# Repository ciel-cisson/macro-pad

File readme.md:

**Présentation du Projet**

Partie Composants 3D

Partie Cuivre 3D

👉 [Liste des composants (à mettre sur github pages)](documents/composants/liste.html)

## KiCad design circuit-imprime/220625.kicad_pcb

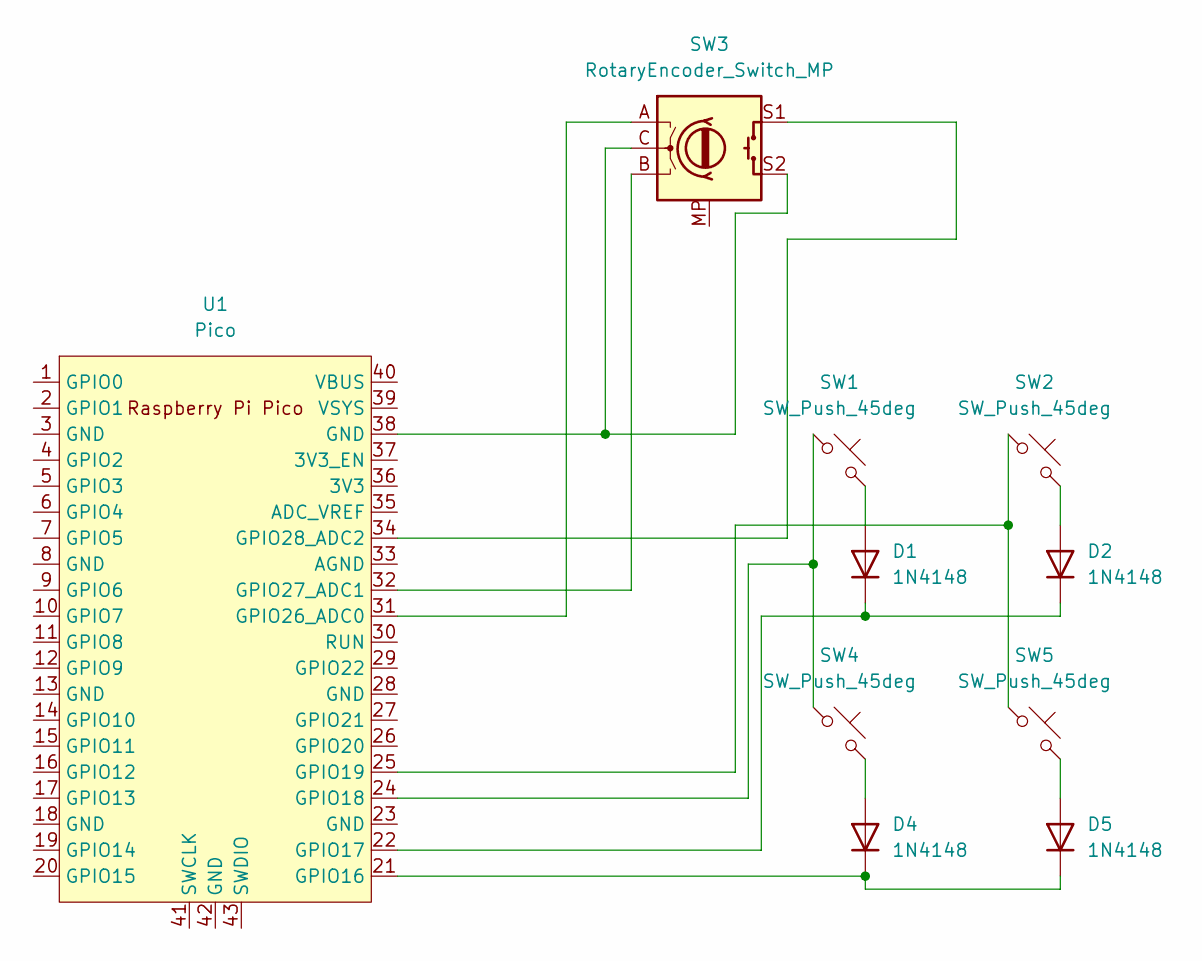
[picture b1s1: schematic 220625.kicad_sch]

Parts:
D1, D2, D4, D5: 1N4148; D_DO-35_SOD27_P7.62mm_Horizontal
SW1, SW2, SW4, SW5: SW_Push_45deg; SW_Cherry_MX_Plate_1.00u
SW3: RotaryEncoder_Switch_MP; RotaryEncoder_Alps_EC11E-Switch_Vertical_H20mm
U1: Pico; RPi_Pico_SMD_TH

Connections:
unnamed: D1.2 (A), SW1.2
unnamed: D1.1 (K), D2.1 (K), U1.22 (GPIO17)
unnamed: D2.2 (A), SW2.2
unnamed: D4.2 (A), SW4.2
unnamed: D4.1 (K), D5.1 (K), U1.21 (GPIO16)
unnamed: D5.2 (A), SW5.2
unnamed: SW3.C, SW3.S2, U1.38 (GND)
unnamed: SW1.1, SW4.1, U1.24 (GPIO18)
unnamed: SW2.1, SW5.1, U1.25 (GPIO19)
unnamed: SW3.A, U1.31 (GPIO26_ADC0)
unnamed: SW3.B, U1.32 (GPIO27_ADC1)
unnamed: SW3.S1, U1.34 (GPIO28_ADC2)

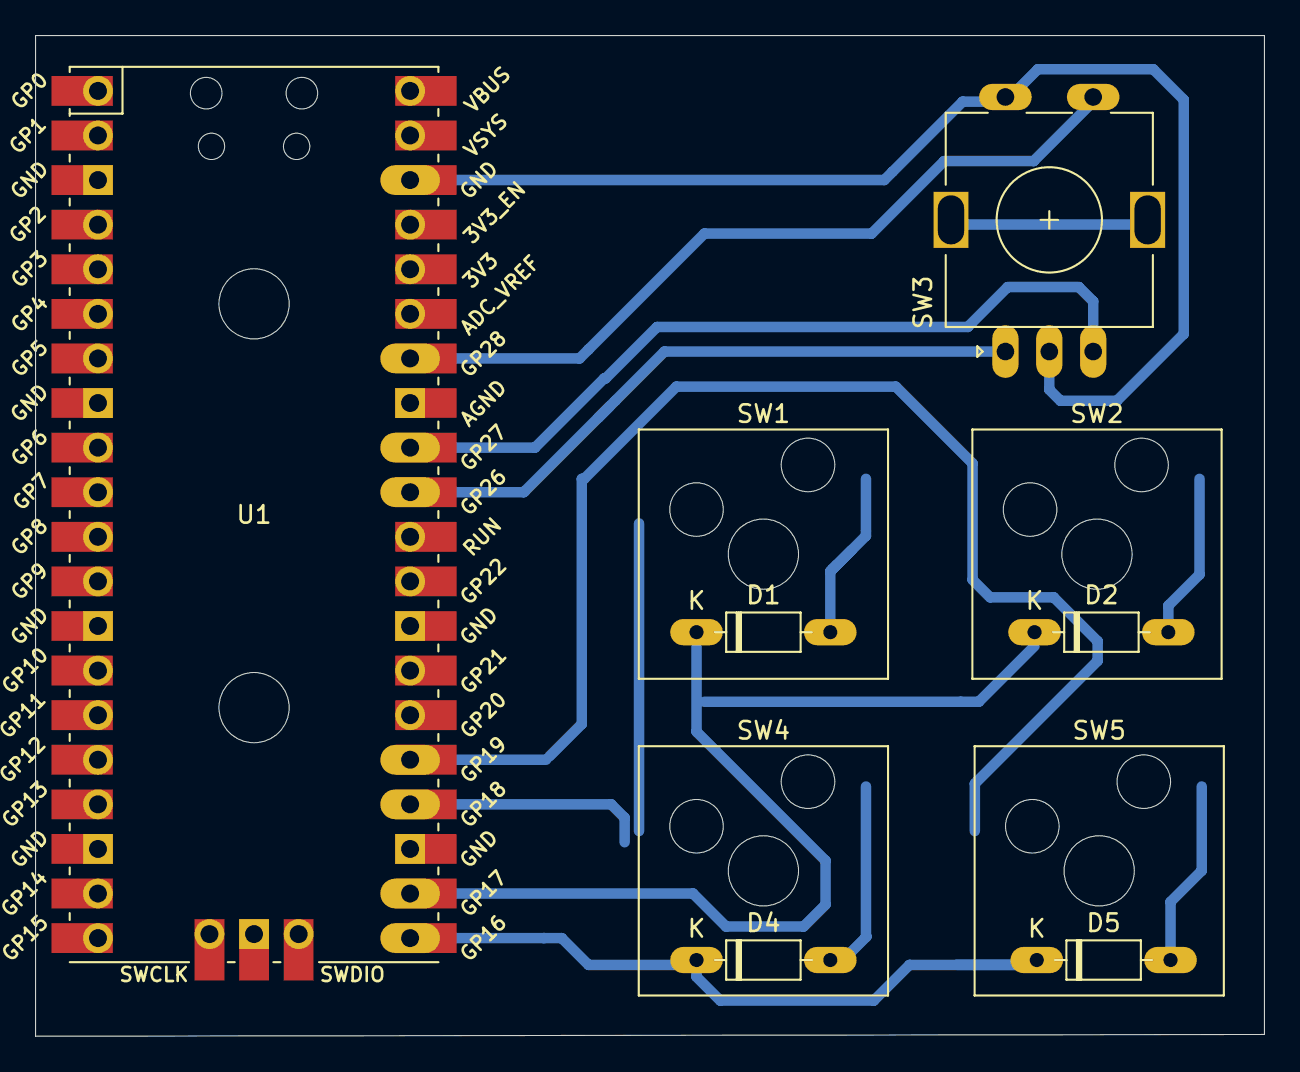
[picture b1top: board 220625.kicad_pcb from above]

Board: 2 copper layers, 70.0 x 57.0 mm, 10 parts (0 on the bottom side), 12 nets.

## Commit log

2025-09-14 Première version du projet
2025-11-16 Version avec Fixations - Déplacement des switchs
2025-11-16 Retrait fichier lourd
2025-11-16 Meilleure découpe des images
2025-11-23 modification du nom du fichier 3D du circuit imprimé
2025-11-23 modification des noms coté cuivre - composants
2025-11-23 modification des liens du fichier readme
2025-11-23 modification du texte du fichier readme
2025-11-23 modification du texte du fichier readme - ajout du terme 3D
2025-11-23 modification orga répertoires
2025-11-23 ajouts de docs techniques sur le pi pico
2025-11-23 correction nom répertoire boitier-3D
2025-11-23 ajout d'une page web pour l'achat des composants
2025-11-23 ajout de la liste.html dans le fichier readme
2025-11-23 ajout de la liste.html dans le fichier readme avec une remarque sur pages
